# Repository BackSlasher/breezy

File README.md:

# Breezy

ESP32 smart-home component for my air conditioner, physically sitting between the HVAC controller and its LCD control panel.

The kit here is a **USP 5010** — controller plus LCD panel (the panel is
marked USP5010BE). If that is what you have, the protocol docs and the
ESPHome components in this repo should work as-is.

Smart-home capability achieved with ESPHome (flashed via USB, OTA available).  
Reads are done by intercepting SPI updates from the AC to the panel.  
Writes are done by emulating IR remote commands.

## In this repo
1. [pcb](pcb/): Board schematics, JLCPCB-ready
2. [esphome/components](esphome/components/): Custom ESPHome components ([example config](esphome/breezy_v4.yaml))
3. [case](case/): scad files for a small case/box for the pcb
4. [docs](docs/): the protocol specs — [the bus](docs/PROTOCOL_BUS.md) and
   [the IR command language](docs/PROTOCOL_IR.md) — plus the working notes
   behind them, and [some photos](docs/photos.md).

## Wiring

Physical wiring:
1. JST 6-wire cable (only 5 actual wires) to AC unit
2. JST 6-wire cable (only 5 actual wires) to LCD panel
3. 220v in (L/N screw terminals) for powering the ESP32 (5v from SPI is weak)

JST wiring is 5v (5v+, gnd, SPI data, SPI clock, IR)

The ESP32 itself is a socketed 38-pin ESP32-WROOM-32 DevKitC-style module
(2×19 headers) — not included on the PCB, plug in your own.

## The protocol, briefly

### Read
The HVAC and its panel talk over a clocked two-wire bus, ~33 ms per cycle.
There are exactly two frames on it:

- a **36-bit LCD status poll** — the controller opens it and goes quiet, and
  the panel answers *inside the same frame* by pulling bits low (the line is
  wired-AND). I don't decode what the panel says; I have no use for it.
- a **76-bit controller status** — the complete unit state, and the one I
  read: power, mode, set temperature, room temperature, fan speed, and
  whether the compressor is actually running right now.

Every bit of the controller status is located and its encoding known, so a
frame can be generated from scratch and checked against the two checksums it
carries. Two flag bits are still unexplained — I know where they are and
when they fire, just not what they mean; one is probably the panel's
backlight. Full field map in [`docs/PROTOCOL_BUS.md`](docs/PROTOCOL_BUS.md).

### Write

The controller is receiving IR commands from a remote via the LCD panel.
The panel holds an IR receiver, demodulates the output and sends the binary on a dedicated wire to the controller, which we can both intercept and send our own.

The IR protocol is reverse engineered completely: any mode, temperature and
fan speed can be composed from scratch, including power-on, which carries the
target state inside the toggle so the unit wakes straight into it. Full spec
in [`docs/PROTOCOL_IR.md`](docs/PROTOCOL_IR.md).

Two things about it are worth knowing before you read anything else:

- **The symbol spelling is the code.** Three of the four pulse shapes mean
  "1", so the same bits can be spelled several ways — and the unit treats
  different spellings as *different commands*.  
  When encoding / decoding, take care to note the length of each part of the pulse (the "on" and the "off" afterwards).
- **24 °C and 25 °C share a temperature byte** and are told apart only by the
  frame being one bit shorter. That one confused me for a while.

## Short version history

Bus pirate worked out of the box for reading, and Arduino R4 bitbanging was enough for writing.  
When moving to dedicated ESP32+PCB, I had to iterate a bit.  
My main pain points were:
1. HVAC wiring didn't contain enough current to power the ESP32, so I needed an external supply and converter
2. HVAC wiring was 5v, and ESP32 operates on 3.3v, so couldn't connect them directly and had to step voltage up/down

- **v1** — BSS138 level shifters with 10K pull-ups. Too slow for the bus; edges rounded off.
- **v2** — TXS0104 shifter, and the board's 5V tied to the panel's,
  either drawing too much current from the panel for it to work,
  or polluting the data with noise from the converter.
- **v3** — 5V properly isolated, but the TXS0104 turned out to be the wrong tool, occasionally misreading the ESP32 as low-driving and pushing that low to the HVAC side, making the panel get garbage data and display nonsense (−9 °C) whenever the ESP32 was powered. It also couldn't read
  and write IR on the same line.
- **v4** — replaced the TXS0104 with plain resistors (high-impedance 100K/180K
  divider taps for reading), and split IR across two ESP32 pins: one read-only
  via a tap, one write-only via an open-collector transistor that pulls the line
  low. For the HVAC components, the board feels like a plain cable.

A recurring pattern was that ESP32 was not a reliable narrator when it had other duties.  
I had several mysteries caused by the ESP32 doing something else (IR transmission, verbose logging) that occupied it enough so it missed bits, generating corrupt or odd frames, both making understanding current state much harder.   
If the measurement is weird, use a dedicated device (another esp32, BusPirate etc)

## ⚠ Mains voltage

This board is powered directly from **220 V AC** through screw terminals on the
PCB. It is a hobby project, not a certified appliance — it has had no safety
testing or approval of any kind. In particular, note it has **no mains-side
fuse**: F1 is a resettable PTC on the 5 V output, and the varistor sits
unfused across L–N. If you build one, you are responsible for
knowing how to work safely with mains, for enclosing it properly, and for
whatever your local regulations require. Don't work on it energised.

## License

MIT — see `LICENSE`.

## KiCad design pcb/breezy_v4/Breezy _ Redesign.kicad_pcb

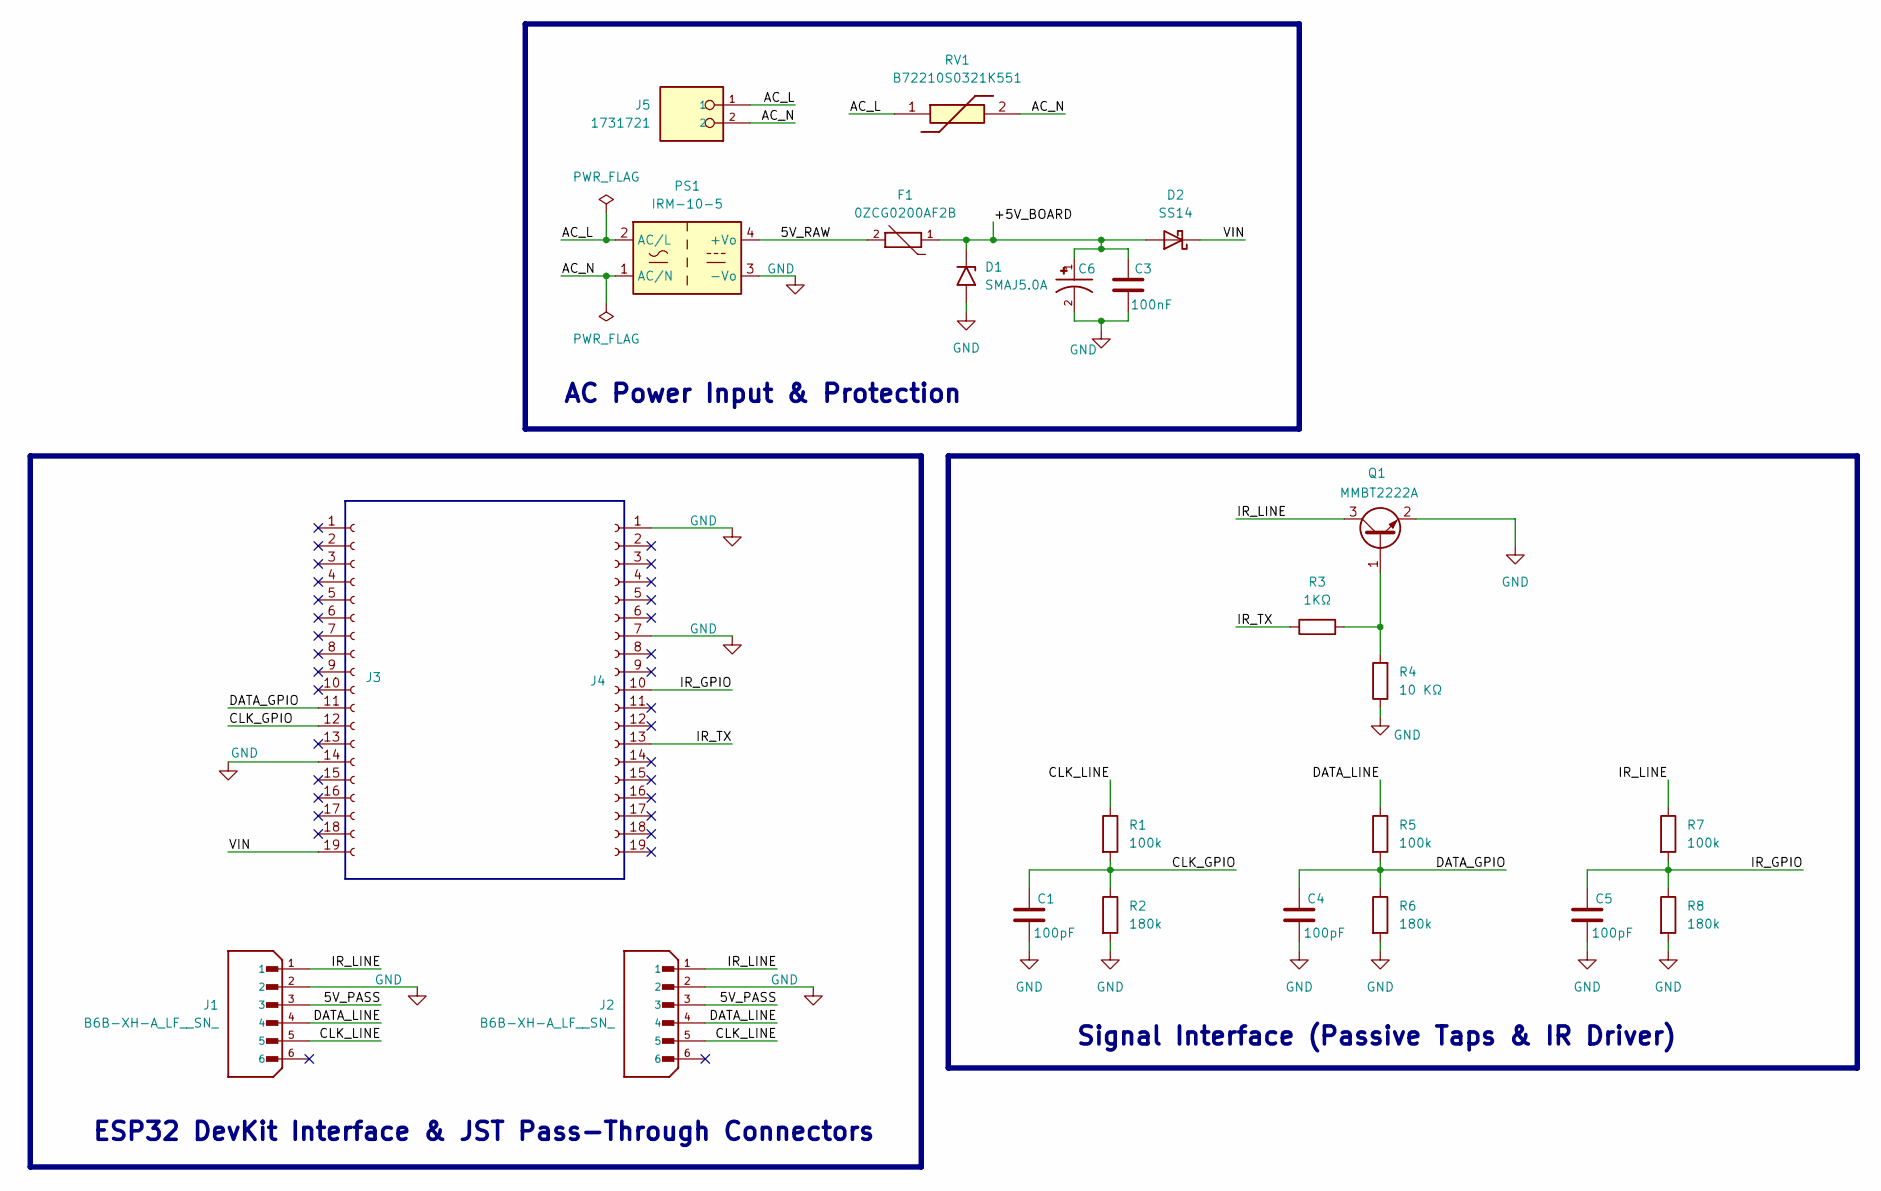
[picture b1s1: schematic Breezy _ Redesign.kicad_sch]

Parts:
C1, C4, C5: 100pF; C_0603_1608Metric
C3: 100nF; C_0603_1608Metric
C6: EEEFK1E101P; CAP_EEEFK1E101P; PARTREV 10-Oct-19
D1: SMAJ5.0A; D_SMA
D2: SS14; D_SMA
F1: 0ZCG0200AF2B; FUSER_0ZCG0200AF2B; PARTREV Apr2023
J1, J2: B6B-XH-A_LF__SN_; JST_B6B-XH-A_LF__SN_; PARTREV 7/4/21
J3, J4: Conn_01x19_Socket; PinSocket_1x19_P2.54mm_Vertical
J5: 1731721; PHOENIX_1731721; PARTREV 16.05.2018
PS1: IRM-10-5; Converter_ACDC_MeanWell_IRM-10-xx_THT
Q1: MMBT2222A; SOT-23
R1, R5, R7: 100k; R_0603_1608Metric
R2, R6, R8: 180k; R_0805_2012Metric
R3: 1KΩ; R_0603_1608Metric
R4: 10 KΩ; R_0603_1608Metric
RV1: B72210S0321K551; Manufacturer_Part_Number B72210S0321K551; Mouser Part Number 871-B72210S0321K551

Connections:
/5V_PASS: J1.3, J2.3
/5V_RAW: F1.2, PS1.4 (+Vo)
/+5V_BOARD: C3.1, C6.1, D1.1 (A1), D2.2 (A), F1.1
/AC_L: J5.1, PS1.2 (AC/L), RV1.1
/AC_N: J5.2, PS1.1 (AC/N), RV1.2
/CLK_GPIO: C1.1, J3.12, R1.2, R2.1
/CLK_LINE: J1.5, J2.5, R1.1
/DATA_GPIO: C4.1, J3.11, R5.2, R6.1
/DATA_LINE: J1.4, J2.4, R5.1
/IR_GPIO: C5.1, J4.10, R7.2, R8.1
/IR_LINE: J1.1, J2.1, Q1.3 (C), R7.1
/IR_TX: J4.13, R3.1
/VIN: D2.1 (K), J3.19
GND: C1.2, C3.2, C4.2, C5.2, C6.2, D1.2 (A2), J1.2, J2.2, J3.14, J4.1, J4.7, PS1.3 (-Vo), Q1.2 (E), R2.2, R4.1, R6.2, R8.2
unnamed: Q1.1 (B), R3.2, R4.2

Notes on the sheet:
ESP32 DevKit Interface & JST Pass-Through Connectors
Signal Interface (Passive Taps & IR Driver)
AC Power Input & Protection

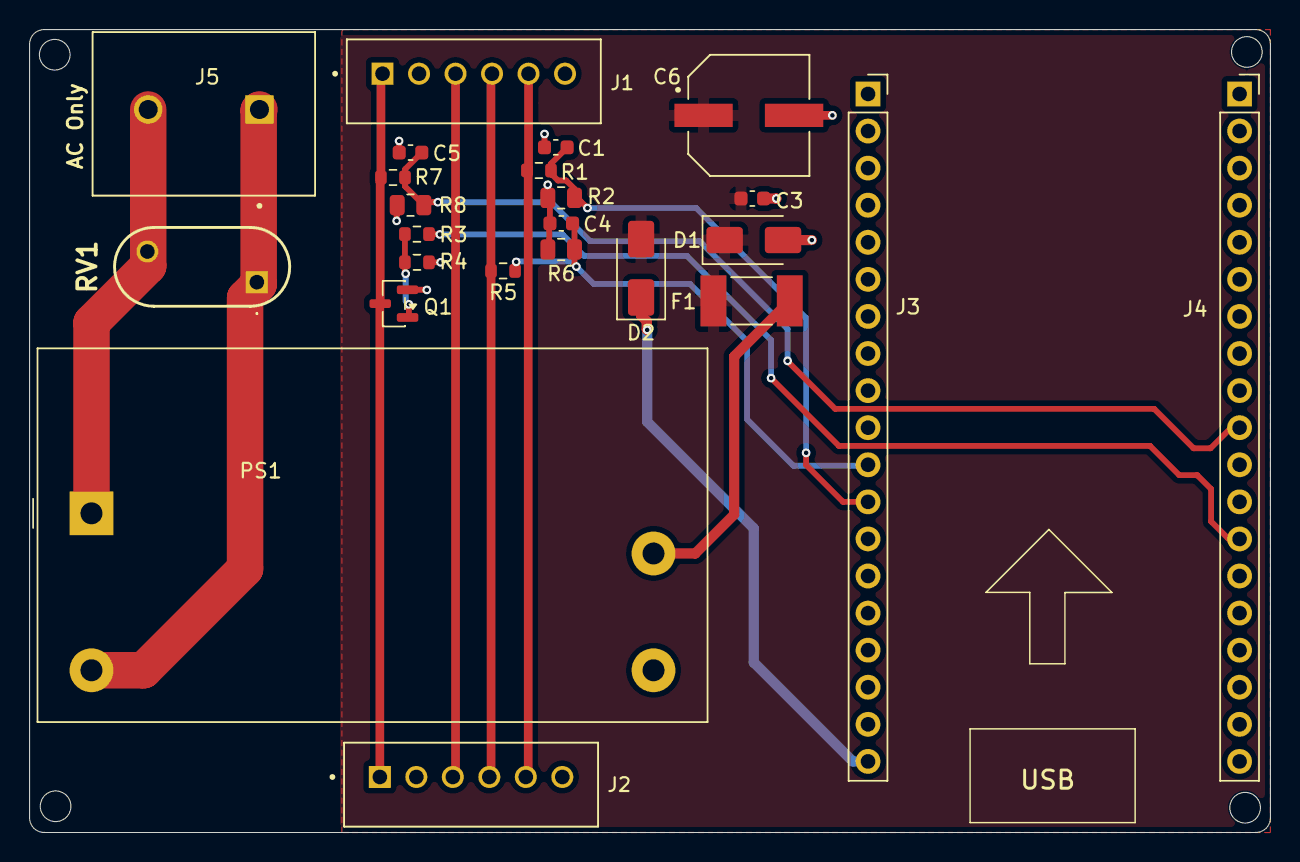
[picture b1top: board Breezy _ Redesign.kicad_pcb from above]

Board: 2 copper layers, 85.0 x 55.0 mm, 24 parts (0 on the bottom side), 15 nets.

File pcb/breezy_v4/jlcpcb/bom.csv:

Designator	Footprint	Quantity	Value	LCSC Part #
"C1, C4, C5"	603	3	100pF	C14858
C3	603	1	100nF	C14663
C6	CAP_EEEFK1E101P	1	EEEFK1E101P	C178539
D1	D_SMA	1	SMAJ5.0A	C908757
D2	D_SMA	1	SS14	C2480
F1	FUSER_0ZCG0200AF2B	1	0ZCG0200AF2B	C5160649
"J1, J2"	JST_B6B-XH-A_LF__SN_	2	B6B-XH-A_LF__SN_	C144397
"J3, J4"	PinSocket_1x19_P2.54mm_Vertical	2	Conn_01x19_Socket	C319202
J5	PHOENIX_1731721	1	1731721	C5443577
PS1	Converter_ACDC_MeanWell_IRM-10-xx_THT	1	IRM-10-5	C2857903
Q1	SOT-23	1	MMBT2222A	C7420351
"R1, R5, R7"	603	3	100k	C25803
"R2, R6, R8"	805	3	180k	C17501
R3	603	1	1K?	C21190
R4	603	1	10 K?	C15401
RV1	B72210S0321K551	1	B72210S0321K551	C210517
